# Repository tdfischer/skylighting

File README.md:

Noisebridge's skylights are boring and dull.

Lets make them shiny shiny!

For more information, check out the canonical wiki page at:

https://noisebridge.net/wiki/Skylighting

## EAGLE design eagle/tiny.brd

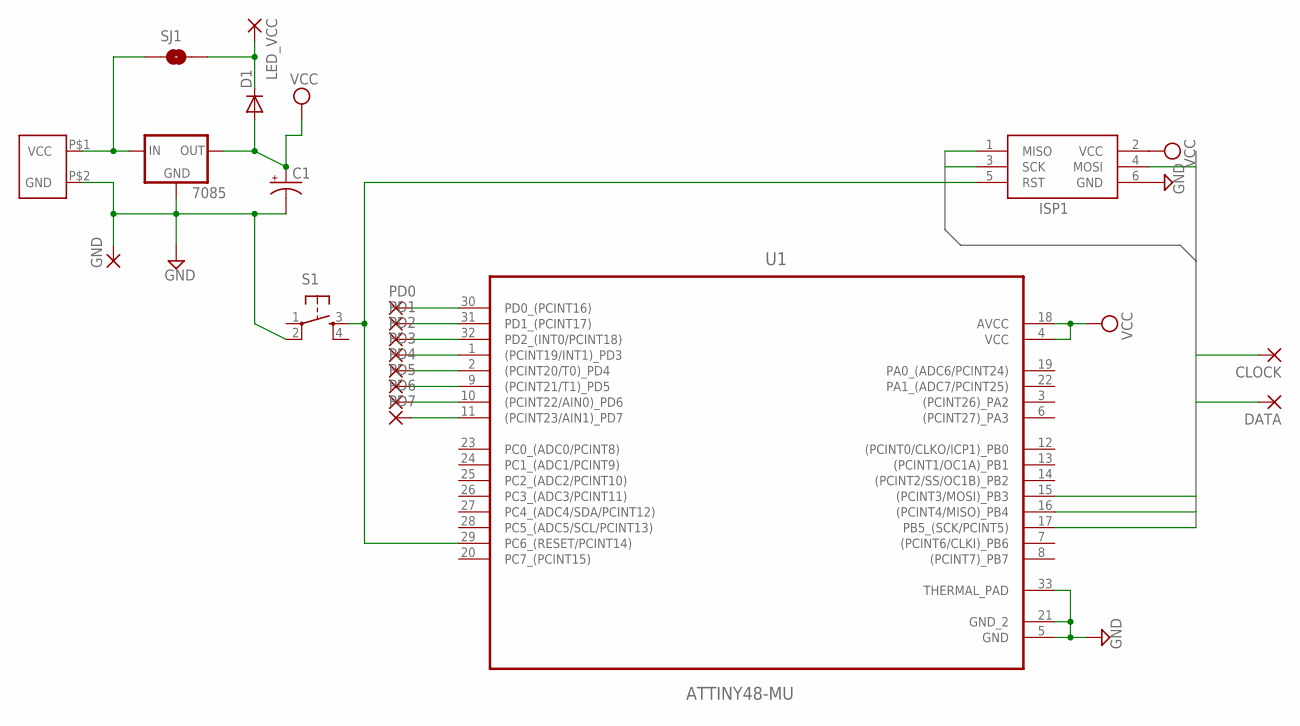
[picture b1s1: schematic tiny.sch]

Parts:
7085: V_REG_78XXSIDE; 78XXL
C1: CPOL-USE2.5-6; E2,5-6
CLOCK: 2,54/1,0
D1: DIODE1N4148; DIODE-1N4148
DATA: 2,54/1,0
GND: 2,54/1,0
ISP1: AVRISP-6; AVRISP
LED_VCC: 2,54/1,0
PD0, PD1, PD2, PD3, PD4, PD5, PD6, PD7: 1,6/0,9
S1: TAC_SWITCHSMD; TACTILE_SWITCH_SMD
SJ1: LED_VCC = VCC; SJ_2S-NO
U1: ATTINY48-MU; QFN50P500X500X100-33N
VCC: OSTOQ023251

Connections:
GND: 7085.GND, C1.-, GND.1, ISP1.6 (GND), S1.2, U1.5 (GND), U1.21 (GND_2), U1.33 (THERMAL_PAD), VCC.P$2 (GND)
MISO: ISP1.1 (MISO), U1.16 ((PCINT4/MISO)_PB4)
MOSI: DATA.1, ISP1.4 (MOSI), U1.15 ((PCINT3/MOSI)_PB3)
unnamed: ISP1.5 (RST), S1.3, U1.29 (PC6_(RESET/PCINT14))
unnamed: 7085.IN, SJ1.1, VCC.P$1 (VCC)
unnamed: PD0.1, U1.30 (PD0_(PCINT16))
unnamed: PD1.1, U1.31 (PD1_(PCINT17))
unnamed: PD2.1, U1.32 (PD2_(INT0/PCINT18))
unnamed: PD3.1, U1.1 ((PCINT19/INT1)_PD3)
unnamed: PD4.1, U1.2 ((PCINT20/T0)_PD4)
unnamed: PD5.1, U1.9 ((PCINT21/T1)_PD5)
unnamed: PD6.1, U1.10 ((PCINT22/AIN0)_PD6)
unnamed: PD7.1, U1.11 ((PCINT23/AIN1)_PD7)
unnamed: D1.C, LED_VCC.1, SJ1.2
SCK: CLOCK.1, ISP1.3 (SCK), U1.17 (PB5_(SCK/PCINT5))
VCC: 7085.OUT, C1.+, D1.A, ISP1.2 (VCC), U1.4 (VCC), U1.18 (AVCC)

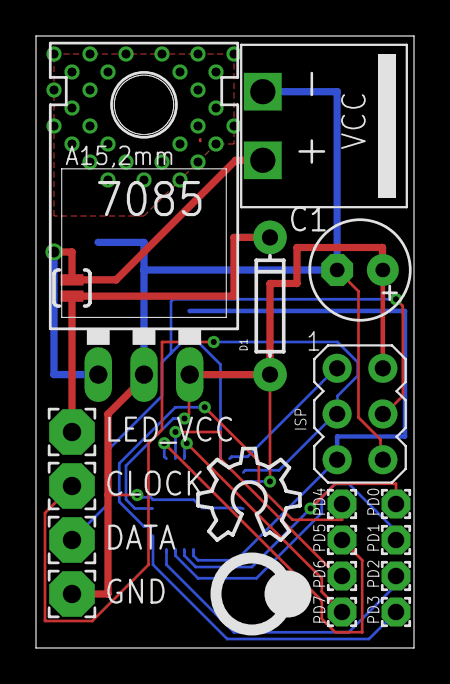
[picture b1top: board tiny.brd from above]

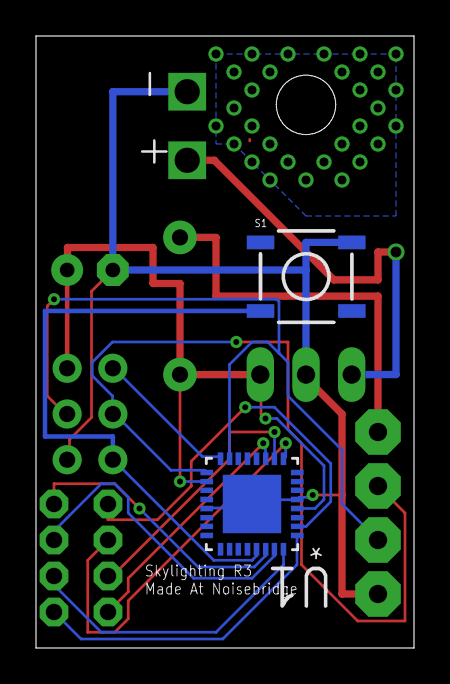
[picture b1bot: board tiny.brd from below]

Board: 2 copper layers, 21.0 x 34.0 mm, 22 parts (2 on the bottom side), 16 nets.

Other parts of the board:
U$1: PHROBO-LOGO
U$2: OSHW_8X200_NOTEXT

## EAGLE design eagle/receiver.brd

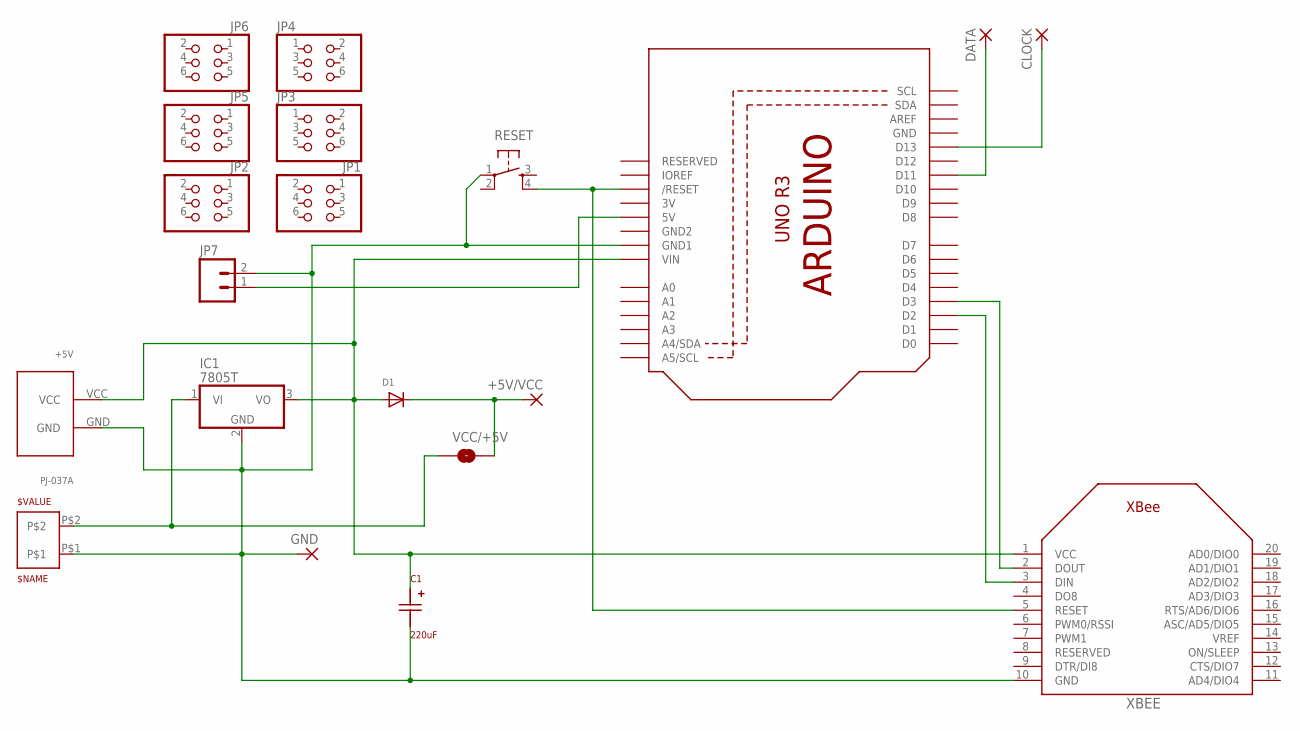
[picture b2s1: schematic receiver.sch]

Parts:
+5V: PJ-037A
+5V/VCC: 2,15/1,0
C1: 220uF; UWT0J221MCL1GB
CLOCK: 2,15/1,0
D1: DIODESOD-323F; SOD-323F
DATA: 2,15/1,0
GND: 2,15/1,0
IC1: 7805T; TO220H
JP1, JP2, JP3, JP4, JP5, JP6: PINHD-2X3; 2X03
JP7: M02PTH; 1X02
RESET: TAC_SWITCHSMD; TACTILE_SWITCH_SMD
U1: ARDUINOR3-DIMENSION; ARDUINOR3
VCC: OSTOQ023251
VCC/+5V: NC=+5v; SJ_2S-NO
XBEE: XBEE

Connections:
3V: U1.3V
GND: +5V.GND, C1.-, GND.1, IC1.2 (GND), JP7.2, RESET.1, U1.GND, U1.GND1, VCC.P$1, XBEE.10 (GND)
GND2: U1.GND2
unnamed: IC1.1 (VI), VCC.P$2, VCC/+5V.1
unnamed: DATA.1, U1.D11
unnamed: CLOCK.1, U1.D13
unnamed: RESET.4, U1.RESET (/RESET), XBEE.5 (RESET)
unnamed: U1.D2, XBEE.3 (DIN)
unnamed: U1.D3, XBEE.2 (DOUT)
unnamed: JP7.1, U1.5V
unnamed: +5V/VCC.1, D1.C, VCC/+5V.2
VCC: +5V.VCC, C1.+, D1.A, IC1.3 (VO), U1.VIN, XBEE.1 (VCC)

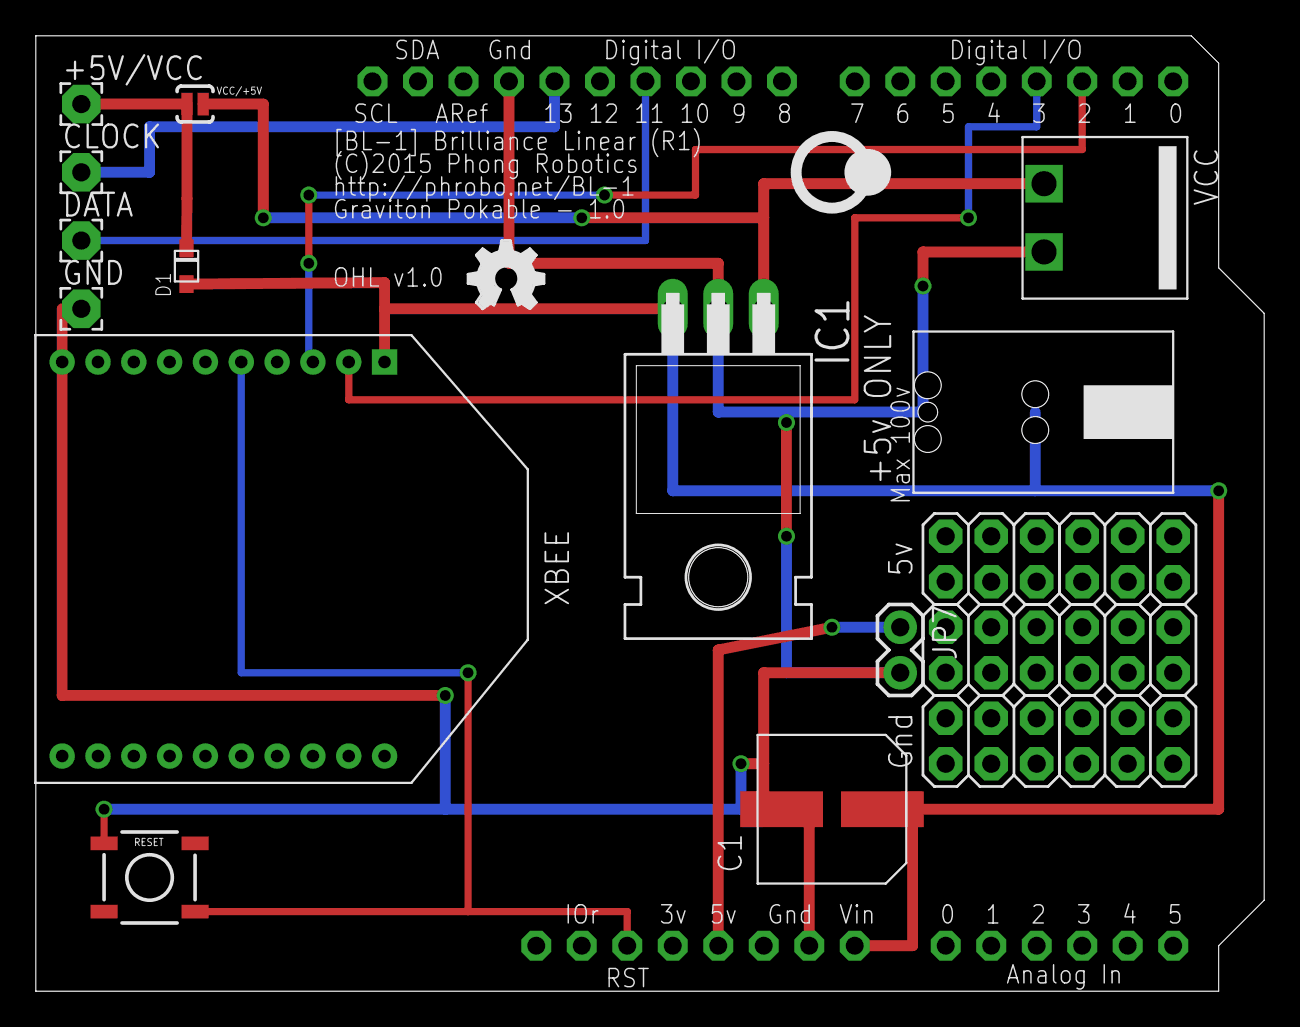
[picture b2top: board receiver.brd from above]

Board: 2 copper layers, 68.6 x 53.3 mm, 22 parts (0 on the bottom side), 10 nets.

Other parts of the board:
U$4: PHROBO-LOGO
U$5: OSHW_FILLX150_NOTEXT

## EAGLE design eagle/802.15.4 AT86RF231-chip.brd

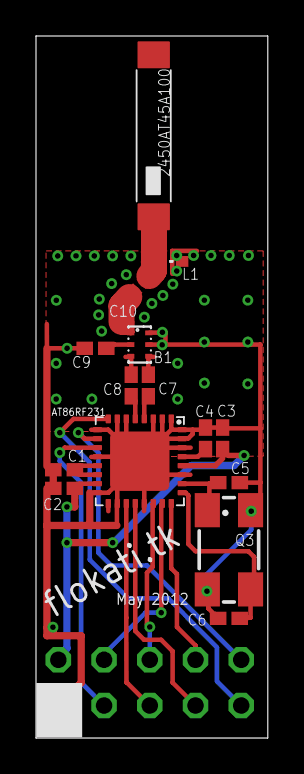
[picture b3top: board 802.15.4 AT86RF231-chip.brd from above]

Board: 2 copper layers, 12.9 x 39.0 mm, 16 parts (1 on the bottom side), 21 nets.

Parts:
AT86RF231: AT86RF231; QFN32
B1: 2450FB15L0001; BALUN
C1, C2, C3, C4: 1uF; C0402K
C5, C6: 12pF; C0402K
C7, C8, C9: 22pF RF; C0402K
C10: 1.5pF; C0402K
L1: 3.9nH; 0402
Q3: 16MHz; CTS406
SV1: FE05-2
U$1: 2450AT45A100

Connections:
/RST: AT86RF231.8, SV1.9
/SEL: AT86RF231.23, SV1.4
ANTENNA: C10.2, L1.2, U$1.P$1
AVDD: AT86RF231.29, C4.2
DIG2: AT86RF231.10, SV1.10
DVDD1: AT86RF231.13, AT86RF231.14, C1.2
GND: AT86RF231.1, AT86RF231.2, AT86RF231.3, AT86RF231.6, AT86RF231.7, AT86RF231.9, AT86RF231.12, AT86RF231.16, AT86RF231.18, AT86RF231.21, AT86RF231.27, AT86RF231.30, AT86RF231.31, AT86RF231.32, AT86RF231.EXP, B1.5, C1.1, C2.2, C3.2, C4.1, C5.2, C6.2, C9.2, L1.1, SV1.1
IRQ: AT86RF231.24, SV1.8
MISO: AT86RF231.20, SV1.7
MOSI: AT86RF231.22, SV1.6
unnamed: AT86RF231.26, C5.1, Q3.1
unnamed: AT86RF231.25, C6.1, Q3.3
unnamed: AT86RF231.4, C8.1
unnamed: AT86RF231.5, C7.2
unnamed: B1.3, C7.1
unnamed: B1.4, C8.2
unnamed: B1.2, C9.1
unnamed: B1.1, C10.1
SCLK: AT86RF231.19, SV1.5
SLP_TR: AT86RF231.11, SV1.3
VCC: AT86RF231.15, AT86RF231.28, C2.1, C3.1, SV1.2

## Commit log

2014-11-10 Add eagle board and LED strip clip
2014-11-10 import wiki page to readme
2014-11-15 Add arduino-mk submodule
2014-11-15 Initial commit of arduino code
2014-11-28 Retool animations to have time-independent frames
2014-11-28 colors: Support brightness values
2014-11-28 Add two new animations
2014-11-28 graviton: Support different kinds of readers
2014-11-28 net: implement a graviton XBee reader
2014-12-16 warning--
2014-12-16 Implement services
2014-12-16 c++11++
2014-12-19 Re-implement call stacks to use a lot less memory
2014-12-19 Start writing a graviton python client
2014-12-19 Export graviton into its own library
2014-12-19 Document graviton-arduino dep
2014-12-26 Shrink the code of the Animation class to bare essentials, and use new graviton static API
2015-01-20 Better power management, improve usability
    - LED strip pins reordered to match most strips
    - Added a reset button
    - Added a diode to protect the arduino from non-5vdc supplies
    - Added a solder jumper to pick between sharing the arduino's 5vdc supply with
    the strip or whatever is on VCC
    - Filter cap on regulator circuit
2015-01-20 Docs++
2015-01-20 Make Animation::step virtual
2015-01-20 Default to idle animation
2015-01-20 Split up the idle animation into distinct sequences
2015-01-28 Parameterize the strip clip and cut a hole in it to reduce LED covering
2015-01-28 Unflip flipped parts
2015-01-28 Add some rounded bits and a support bridge for deposition printers
2015-04-04 First draft of the tiny skylighting variant
2015-05-16 Port to use fastled
2015-05-17 Fix all the color fading bugs in the twinkle anim
2015-05-23 Add a demo of the playa
2015-06-04 Add some explanation
2015-06-04 Add fastled library
2015-06-04 Add some throbbing animation
2015-06-04 Make a tiny prototype of skylighting
2015-06-04 Ignore all build output
2015-06-04 Ignore more intermediate files
2015-06-04 reorganize python bits, and add some more
2015-06-04 import an at86rf231 breakout board
2015-06-04 Add a simple blink smoke test
2015-06-04 Port demo from master

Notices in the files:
eagle/receiver.brd:
(C)2015 Phong Robotics
parts and their libraries:
SparkFun: Licensing: CC v3.0 Share-Alike You are welcome to use this library for commercial purposes.
wuerth-elektronik: Copyright: Würth Elektronik eiSos
